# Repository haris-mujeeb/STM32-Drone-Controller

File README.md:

# 🚁 STM32 Drone Controller 🚀

A compact and robust drone flight controller designed with STM32 microcontroller and KiCad. This project focuses on providing a reliable hardware platform for custom drone builds and research.

## ✨ Features

*   **STM32 Microcontroller**: High-performance processing for flight control algorithms.
*   **BMI088 IMU**: Integrated 6-axis Inertial Measurement Unit for precise attitude estimation.
*   **KiCad Design**: Open-source hardware design files for easy modification and manufacturing.

## 🛠️ Technologies Used

*   **KiCad**: PCB design and schematic capture.
*   **STM32**: Embedded system development.
*   **BMI088**: Sensor integration.

## 📸 Visuals

## 📍Pinout

## 📄Schematic

## 📂 Project Structure

The repository contains all necessary KiCad project files, component libraries, and documentation.

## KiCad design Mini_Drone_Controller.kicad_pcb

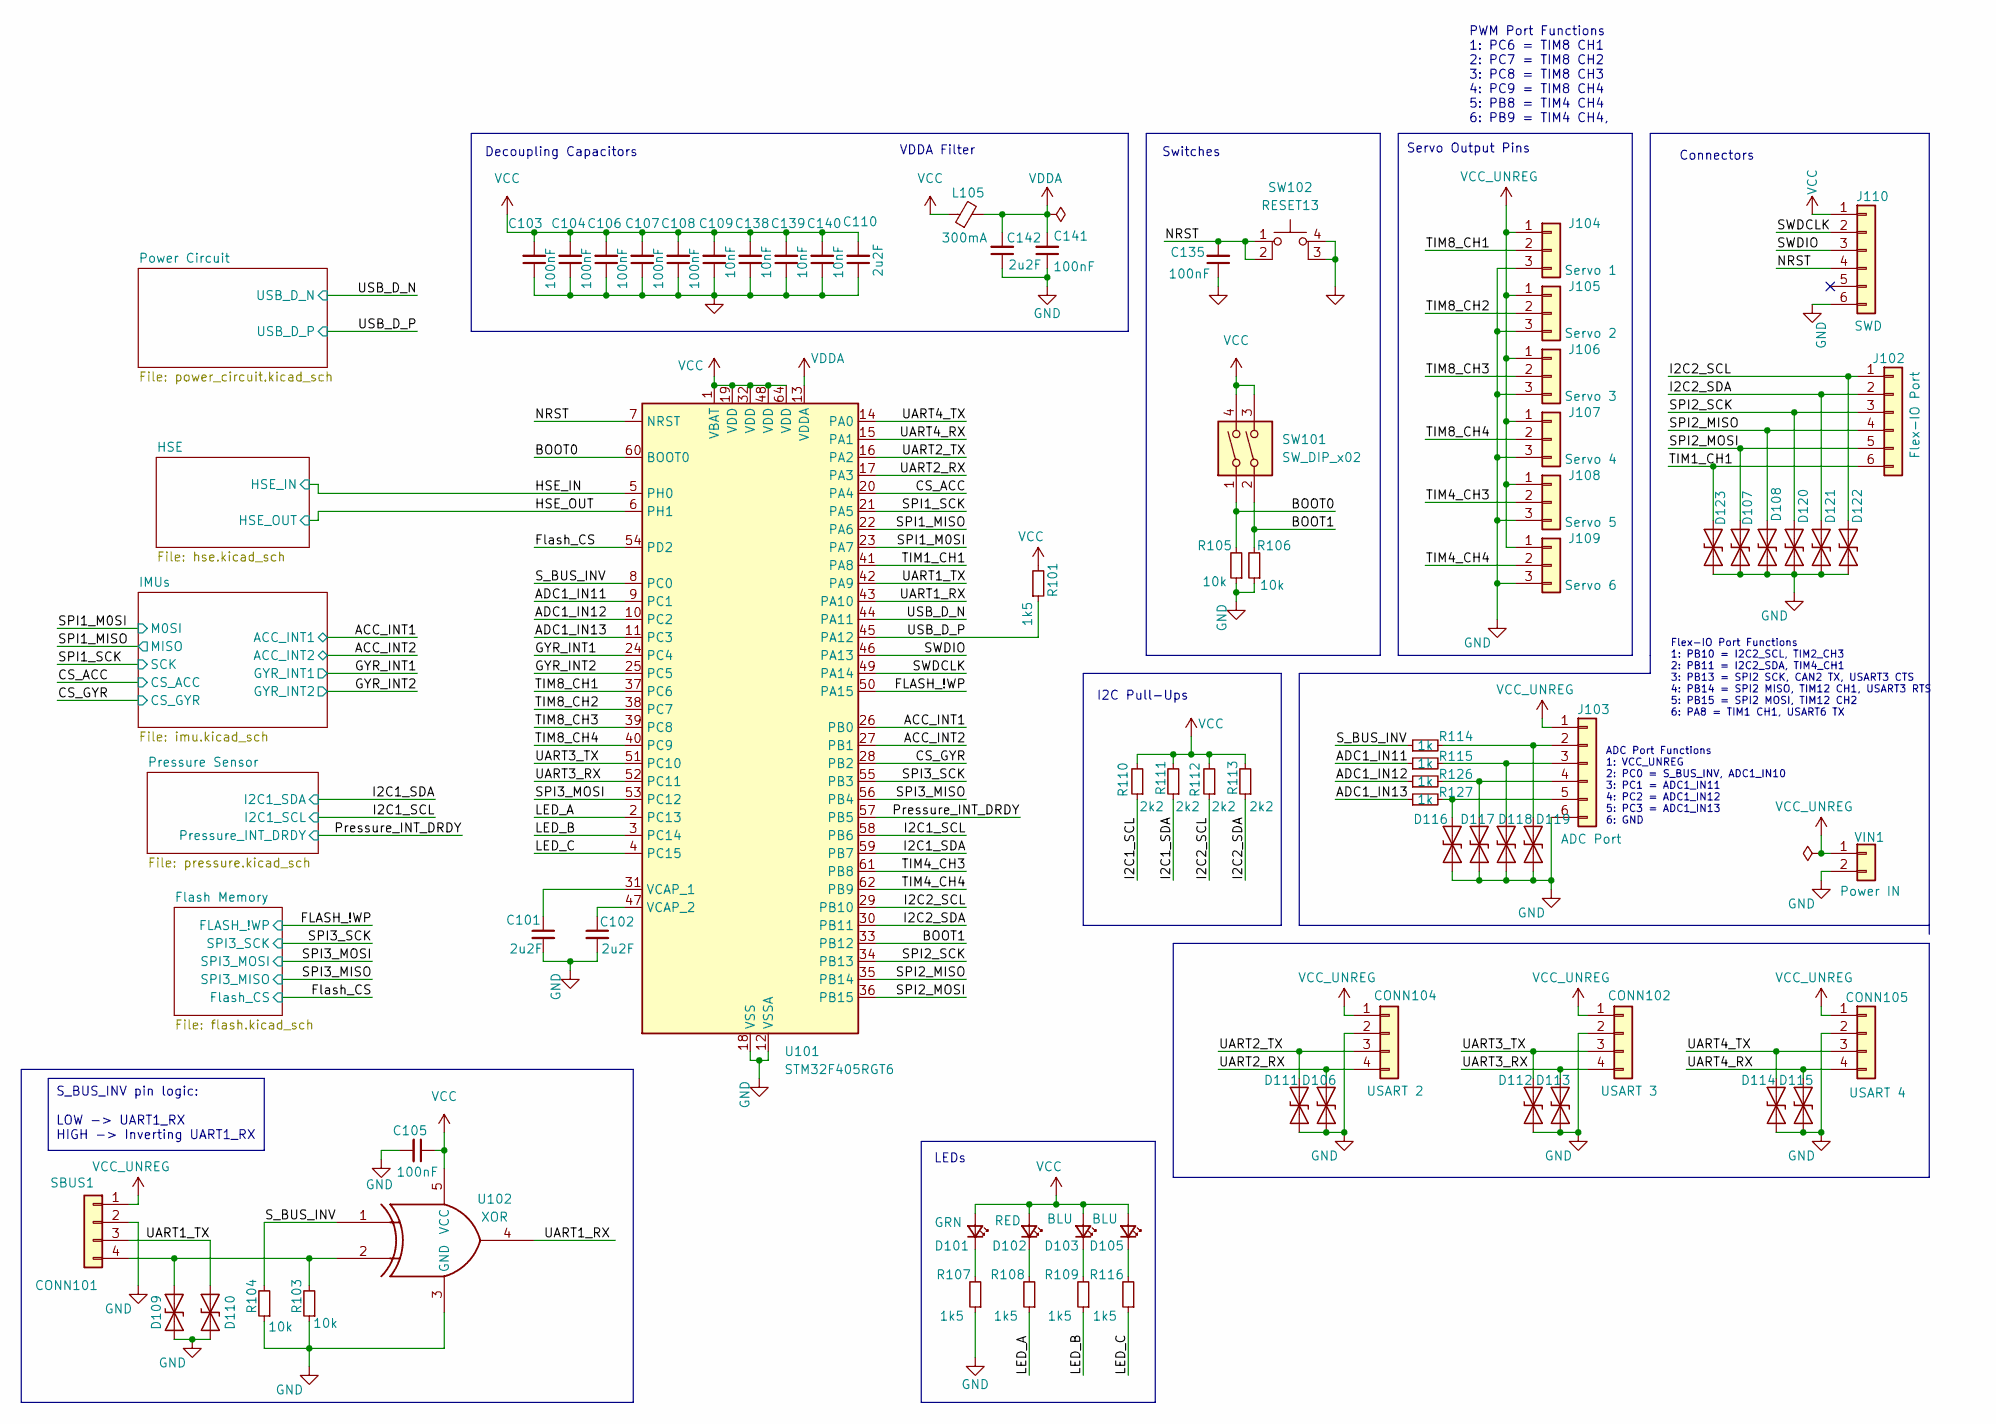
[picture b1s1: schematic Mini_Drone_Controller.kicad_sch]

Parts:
C101, C102, C110, C142: 2u2F; C_0402_1005Metric; Mfr. # CL05A225MQ5NSNC
C103, C104, C105, C106, C107, C108, C135, C141: 100nF; C_0402_1005Metric; Mfr. # CL05B104KO5NNNC
C109, C138, C139, C140: 10nF; C_0402_1005Metric; Mfr. # CL05B103KB5NNNC
CONN101: SBUS1; PinHeader_1x04_P2.54mm_Vertical; Mfr. # HB-PH3-25414PB2GOP
CONN102: USART 3; PinHeader_1x04_P2.54mm_Vertical; Mfr. # HB-PH3-25414PB2GOP
CONN104: USART 2; PinHeader_1x04_P2.54mm_Vertical; Mfr. # HB-PH3-25414PB2GOP
CONN105: USART 4; PinHeader_1x04_P2.54mm_Vertical; Mfr. # HB-PH3-25414PB2GOP
D101: GRN; LED_0603_1608Metric; Mfr. # PSC-1608U52GC-G4
D102: RED; LED_0603_1608Metric; Mfr. # XL-1608SURC-06
D103, D105: BLU; LED_0603_1608Metric; Mfr. # XL-1608UBC-04
D106, D107, D108, D109, D110, D111, D112, D113, D114, D115, D116, D117, D118, D119, D120, D121, D122, D123: ESD9B3.3ST5G; D_SOD-923; Mfr. # ESD9B3.3ST5G
J102: Flex-IO Port; PinHeader_1x06_P2.54mm_Vertical; Mfr. # PZ254V-11-06P
J103: ADC Port; PinHeader_1x06_P2.54mm_Vertical; Mfr. # PZ254V-11-06P
J104: Servo 1; PinHeader_1x03_P2.54mm_Vertical; Mfr. # 2.54-1*3P
J105: Servo 2; PinHeader_1x03_P2.54mm_Vertical; Mfr. # 2.54-1*3P
J106: Servo 3; PinHeader_1x03_P2.54mm_Vertical; Mfr. # 2.54-1*3P
J107: Servo 4; PinHeader_1x03_P2.54mm_Vertical; Mfr. # 2.54-1*3P
J108: Servo 5; PinHeader_1x03_P2.54mm_Vertical; Mfr. # 2.54-1*3P
J109: Servo 6; PinHeader_1x03_P2.54mm_Vertical; Mfr. # 2.54-1*3P
J110: SWD; PinHeader_1x06_P2.54mm_Vertical; Mfr. # PZ254V-11-06P
L105: 300mA; R_0402_1005Metric; Mfr. # BLM15AG102SN1D
R101, R107, R108, R109, R116: 1k5; R_0402_1005Metric; Mfr. # RC0402FR-071K5L
R103, R104, R105, R106: 10k; R_0402_1005Metric; Mfr. # RC0402FR-0710KL
R110, R111, R112, R113: 2k2; R_0402_1005Metric; Mfr. # RC0402FR-072K2L
R114, R115, R126, R127: 1k; R_0402_1005Metric; Mfr. # RC0402FR-071KL
SW101: SW_DIP_x02; SW_DIP_SPSTx02_Slide_Copal_CHS-02B_W7.62mm_P1.27mm; Mfr. # DSHP02TSGET
SW102: RESET13; SW_DIP_SPSTx01_Slide_Copal_CHS-01A_W5.08mm_P1.27mm_JPin; Mfr. # TS-1088-AR02016
U101: STM32F405RGT6; LQFP-64_10x10mm_P0.5mm; Mfr. # STM32F405RGT6
U102: XOR; SOT-353_SC-70-5; Mfr. # SN74LVC1G86DCKR
VIN1: Power IN; PinHeader_1x02_P2.54mm_Vertical; Mfr. # PZ254V-11-02P

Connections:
/ACC_INT1: U101.26 (PB0); also elsewhere on the board
/ACC_INT2: U101.27 (PB1); also elsewhere on the board
/ADC1_IN11: R115.1, U101.9 (PC1)
/ADC1_IN12: R126.1, U101.10 (PC2)
/ADC1_IN13: R127.1, U101.11 (PC3)
/BOOT0: R105.2, SW101.1, U101.60 (BOOT0)
/BOOT1: R106.2, SW101.2, U101.33 (PB12)
/CS_ACC: U101.20 (PA4); also elsewhere on the board
/CS_GYR: U101.28 (PB2); also elsewhere on the board
/FLASH_!WP: U101.50 (PA15); also elsewhere on the board
/Flash_CS: U101.54 (PD2); also elsewhere on the board
/GYR_INT1: U101.24 (PC4); also elsewhere on the board
/GYR_INT2: U101.25 (PC5); also elsewhere on the board
/HSE_IN: U101.5 (PH0); also elsewhere on the board
/HSE_OUT: U101.6 (PH1); also elsewhere on the board
/I2C1_SCL: R110.1, U101.58 (PB6); also elsewhere on the board
/I2C1_SDA: R111.1, U101.59 (PB7); also elsewhere on the board
/I2C2_SCL: D122.2 (A2), J102.1, R112.1, U101.29 (PB10)
/I2C2_SDA: D121.2 (A2), J102.2, R113.1, U101.30 (PB11)
/LED_A: R108.1, U101.2 (PC13)
/LED_B: R109.1, U101.3 (PC14)
/LED_C: R116.1, U101.4 (PC15)
/NRST: C135.2, J110.4, SW102.1, SW102.2, U101.7 (NRST)
/Pressure_INT_DRDY: U101.57 (PB5); also elsewhere on the board
/SPI1_M0SI: U101.23 (PA7); also elsewhere on the board
/SPI1_MISO: U101.22 (PA6); also elsewhere on the board
/SPI1_SCK: U101.21 (PA5); also elsewhere on the board
/SPI2_MISO: D108.2 (A2), J102.4, U101.35 (PB14)
/SPI2_MOSI: D107.2 (A2), J102.5, U101.36 (PB15)
/SPI2_SCK: D120.2 (A2), J102.3, U101.34 (PB13)
/SPI3_MISO: U101.56 (PB4); also elsewhere on the board
/SPI3_MOSI: U101.53 (PC12); also elsewhere on the board
/SPI3_SCK: U101.55 (PB3); also elsewhere on the board
/SWDCLK: J110.2, U101.49 (PA14)
/SWDIO: J110.3, U101.46 (PA13)
/S_BUS_INV: R104.2, R114.1, U101.8 (PC0), U102.1
/TIM1_CH1: D123.2 (A2), J102.6, U101.41 (PA8)
/TIM4_CH3: J108.2, U101.61 (PB8)
/TIM4_CH4: J109.2, U101.62 (PB9)
/TIM8_CH1: J104.2, U101.37 (PC6)
/TIM8_CH2: J105.2, U101.38 (PC7)
/TIM8_CH3: J106.2, U101.39 (PC8)
/TIM8_CH4: J107.2, U101.40 (PC9)
/UART1_RX: U101.43 (PA10), U102.4
/UART1_TX: CONN101.3, D110.2 (A2), U101.42 (PA9)
/UART2_RX: CONN104.4, D106.2 (A2), U101.17 (PA3)
/UART2_TX: CONN104.3, D111.2 (A2), U101.16 (PA2)
/UART3_RX: CONN102.4, D113.2 (A2), U101.52 (PC11)
/UART3_TX: CONN102.3, D112.2 (A2), U101.51 (PC10)
/UART4_RX: CONN105.4, D115.2 (A2), U101.15 (PA1)
/UART4_TX: CONN105.3, D114.2 (A2), U101.14 (PA0)
/USB_D_N: U101.44 (PA11); also elsewhere on the board
/USB_D_P: R101.1, U101.45 (PA12); also elsewhere on the board
GND: C101.2, C102.2, C103.1, C104.1, C105.2, C106.1, C107.1, C108.1, C109.1, C110.1, C135.1, C138.1, C139.1, C140.1, C141.1, C142.1, CONN101.2, CONN102.2, CONN104.2, CONN105.2, D106.1 (A1), D107.1 (A1), D108.1 (A1), D109.1 (A1), D110.1 (A1), D111.1 (A1), D112.1 (A1), D113.1 (A1), D114.1 (A1), D115.1 (A1), D116.1 (A1), D117.1 (A1), D118.1 (A1), D119.1 (A1), D120.1 (A1), D121.1 (A1), D122.1 (A1), D123.1 (A1), J103.6, J104.3, J105.3, J106.3, J107.3, J108.3, J109.3, J110.6, R103.1, R104.1, R105.1, R106.1, R107.1, SW102.3 (K), SW102.4 (A), U101.12 (VSSA), U101.18 (VSS), U101.63 (VSS), U102.3 (GND), VIN1.2; also elsewhere on the board
unnamed: CONN101.4, D109.2 (A2), R103.2, U102.2
unnamed: D101.1 (K), R107.2
unnamed: D102.1 (K), R108.2
unnamed: D103.1 (K), R109.2
unnamed: D105.1 (K), R116.2
unnamed: D116.2 (A2), J103.5, R127.2
unnamed: D117.2 (A2), J103.4, R126.2
unnamed: D118.2 (A2), J103.3, R115.2
unnamed: D119.2 (A2), J103.2, R114.2
unnamed: C101.1, U101.31 (VCAP_1)
unnamed: C102.1, U101.47 (VCAP_2)
VCC: C103.2, C104.2, C105.1, C106.2, C107.2, C108.2, C109.2, C110.2, C138.2, C139.2, C140.2, D101.2 (A), D102.2 (A), D103.2 (A), D105.2 (A), J110.1, L105.1, R101.2, R110.2, R111.2, R112.2, R113.2, SW101.3, SW101.4, U101.1 (VBAT), U101.19 (VDD), U101.32 (VDD), U101.48 (VDD), U101.64 (VDD), U102.5 (VCC); also elsewhere on the board
VCC_UNREG: CONN101.1, CONN102.1, CONN104.1, CONN105.1, J103.1, J104.1, J105.1, J106.1, J107.1, J108.1, J109.1, VIN1.1; also elsewhere on the board
VDDA: C141.2, C142.2, L105.2, U101.13 (VDDA)

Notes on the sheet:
S_BUS_INV pin logic: LOW -> UART1_RX HIGH -> Inverting UART1_RX
LEDs
Switches
Connectors
Decoupling Capacitors
VDDA Filter
Flex-IO Port Functions 1: PB10 = I2C2_SCL, TIM2_CH3 2: PB11 = I2C2_SDA, TIM4_CH1 3: PB13 = SPI2 SCK, CAN2 TX, USART3 CTS 4: PB14 = SPI2 MISO, TIM12 CH1, USART3 RTS 5: PB15 = SPI2 MOSI, TIM12 CH2 6: PA8 = TIM1 CH1, USART6 TX
I2C Pull-Ups
PWM Port Functions 1: PC6 = TIM8 CH1 2: PC7 = TIM8 CH2 3: PC8 = TIM8 CH3 4: PC9 = TIM8 CH4 5: PB8 = TIM4 CH4 6: PB9 = TIM4 CH4,
ADC Port Functions 1: VCC_UNREG 2: PC0 = S_BUS_INV, ADC1_IN10 3: PC1 = ADC1_IN11 4: PC2 = ADC1_IN12 5: PC3 = ADC1_IN13 6: GND
Servo Output Pins

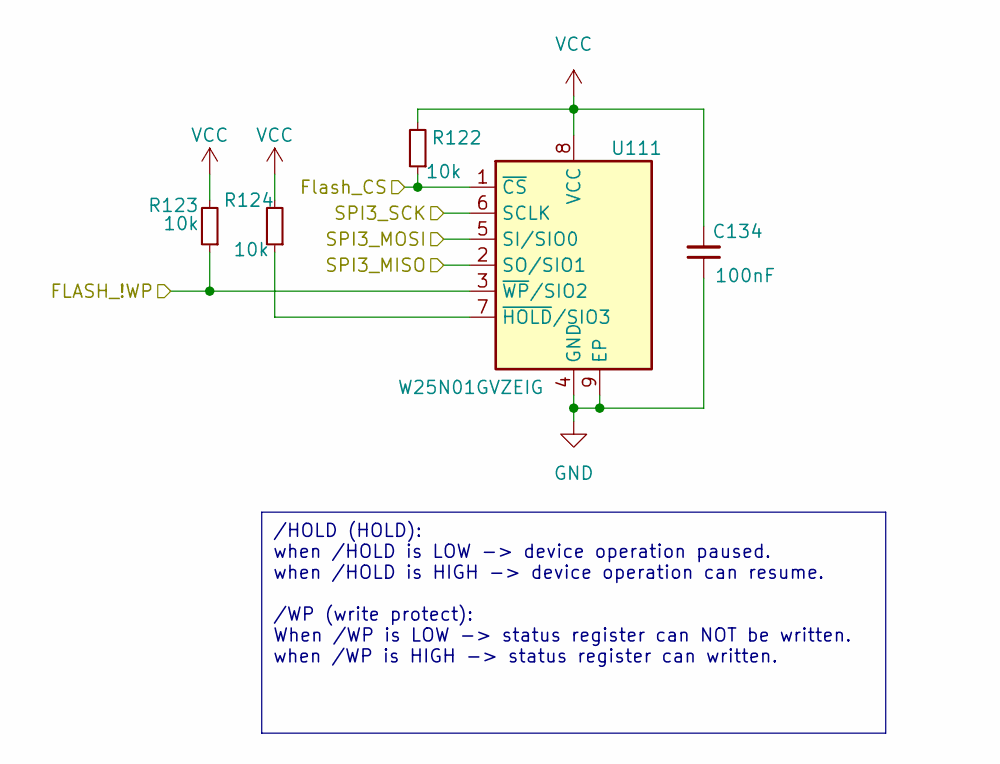
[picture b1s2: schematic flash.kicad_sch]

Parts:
C134: 100nF; C_0402_1005Metric; Mfr. # CL05B104KO5NNNC
R122, R123, R124: 10k; R_0402_1005Metric; Mfr. # RC0402FR-0710KL
U111: W25N01GVZEIG; WSON-8-1EP_8x6mm_P1.27mm_EP3.4x4.3mm; Mfr. # W25N01GVZEIG

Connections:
/FLASH_!WP: R123.1, U111.3 (~WP/SIO2); also elsewhere on the board
/Flash_CS: R122.1, U111.1 (~CS); also elsewhere on the board
/SPI3_MISO: U111.2 (SO/SIO1); also elsewhere on the board
/SPI3_MOSI: U111.5 (SI/SIO0); also elsewhere on the board
/SPI3_SCK: U111.6 (SCLK); also elsewhere on the board
GND: C134.1, U111.4 (GND), U111.9 (EP); also elsewhere on the board
unnamed: R124.1, U111.7 (~HOLD/SIO3)
VCC: C134.2, R122.2, R123.2, R124.2, U111.8 (VCC); also elsewhere on the board

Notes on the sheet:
/HOLD (HOLD): when /HOLD is LOW -> device operation paused. when /HOLD is HIGH -> device operation can resume. /WP (write protect): When /WP is LOW -> status register can NOT be written. when /WP is HIGH -> status register can written.

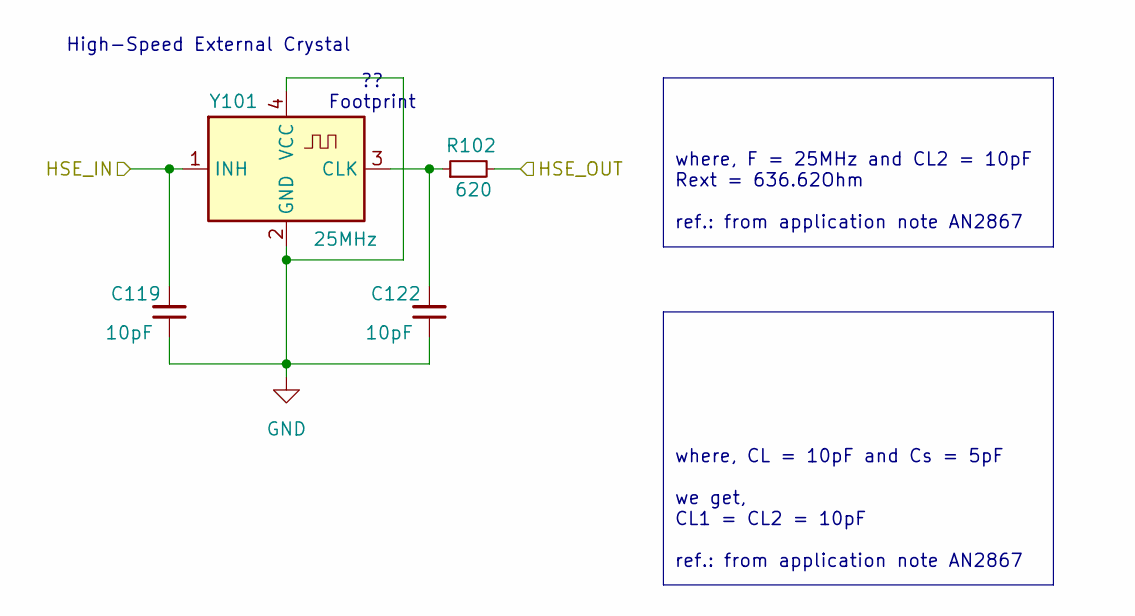
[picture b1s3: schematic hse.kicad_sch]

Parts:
C119, C122: 10pF; C_0402_1005Metric; Mfr. # CL05C100JB5NNNC
R102: 620; R_0402_1005Metric; Mfr. # RC0402FR-07620RL
Y101: 25MHz; Oscillator_SMD_Kyocera_KC2520Z-4Pin_2.5x2.0mm; Mfr. # X322525MSB4SI

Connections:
/HSE_IN: C119.2, Y101.1 (INH); also elsewhere on the board
/HSE_OUT: R102.2; also elsewhere on the board
GND: C119.1, C122.1, Y101.2 (GND), Y101.4 (VCC); also elsewhere on the board
unnamed: C122.2, R102.1, Y101.3 (CLK)

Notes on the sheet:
where, CL = 10pF and Cs = 5pF we get, CL1 = CL2 = 10pF ref.: from application note AN2867
where, F = 25MHz and CL2 = 10pF Rext = 636.62Ohm ref.: from application note AN2867
?? Footprint
High-Speed External Crystal

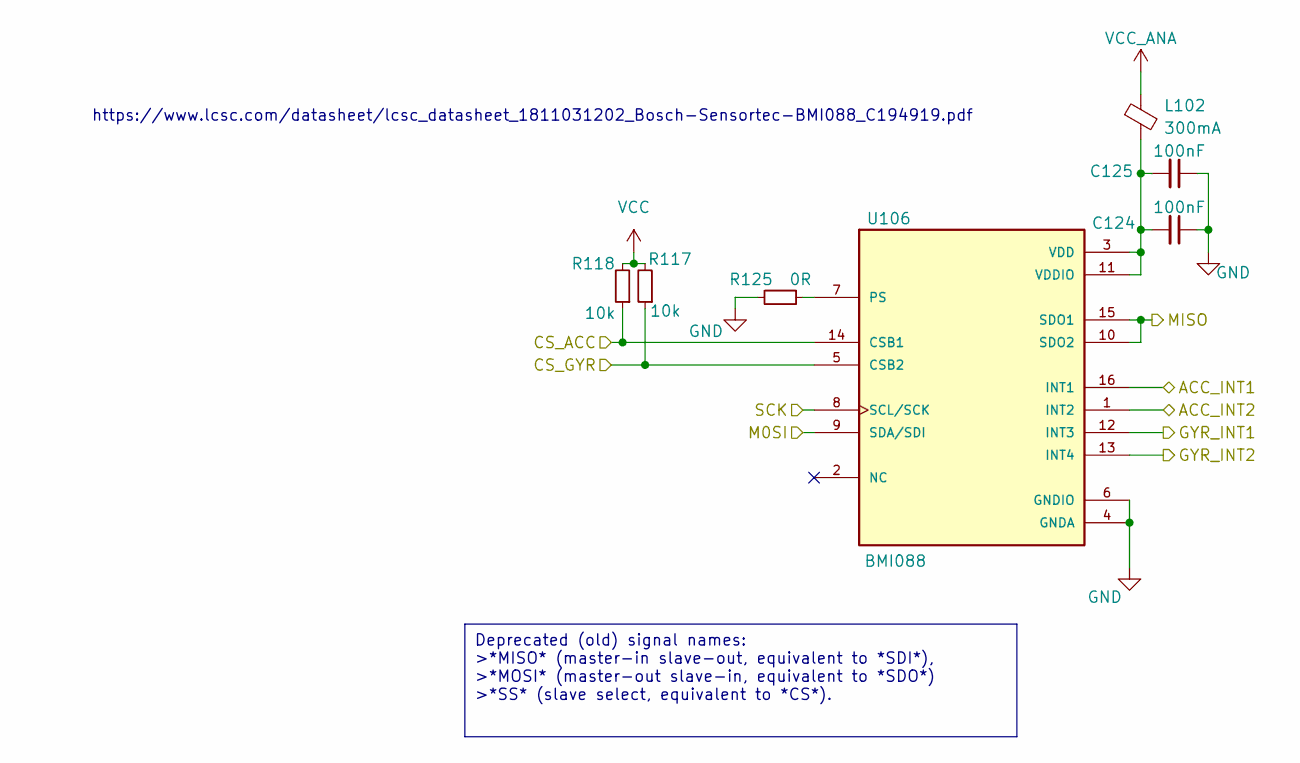
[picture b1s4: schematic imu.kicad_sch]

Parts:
C124, C125: 100nF; C_0402_1005Metric; Mfr. # CL05B104KO5NNNC
L102: 300mA; R_0402_1005Metric; Mfr. # BLM15AG102SN1D
R117, R118: 10k; R_0402_1005Metric; Mfr. # RC0402FR-0710KL
R125: 0R; R_0402_1005Metric; Mfr. # RC0402JR-070RL
U106: BMI088; PQFN50P450X300X100-16N; Mfr. # BMI088

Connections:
/ACC_INT1: U106.16 (INT1); also elsewhere on the board
/ACC_INT2: U106.1 (INT2); also elsewhere on the board
/CS_ACC: R118.1, U106.14 (CSB1); also elsewhere on the board
/CS_GYR: R117.1, U106.5 (CSB2); also elsewhere on the board
/GYR_INT1: U106.12 (INT3); also elsewhere on the board
/GYR_INT2: U106.13 (INT4); also elsewhere on the board
/SPI1_M0SI: U106.9 (SDA/SDI); also elsewhere on the board
/SPI1_MISO: U106.10 (SDO2), U106.15 (SDO1); also elsewhere on the board
/SPI1_SCK: U106.8 (SCL/SCK); also elsewhere on the board
GND: C124.1, C125.1, R125.2, U106.4 (GNDA), U106.6 (GNDIO); also elsewhere on the board
unnamed: R125.1, U106.7 (PS)
unnamed: C124.2, C125.2, L102.2, U106.3 (VDD), U106.11 (VDDIO)
VCC: R117.2, R118.2; also elsewhere on the board
VCC_ANA: L102.1; also elsewhere on the board

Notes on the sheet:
Deprecated (old) signal names: >*MISO* (master-in slave-out, equivalent to *SDI*), >*MOSI* (master-out slave-in, equivalent to *SDO*) >*SS* (slave select, equivalent to *CS*).
https://www.lcsc.com/datasheet/lcsc_datasheet_1811031202_Bosch-Sensortec-BMI088_C194919.pdf

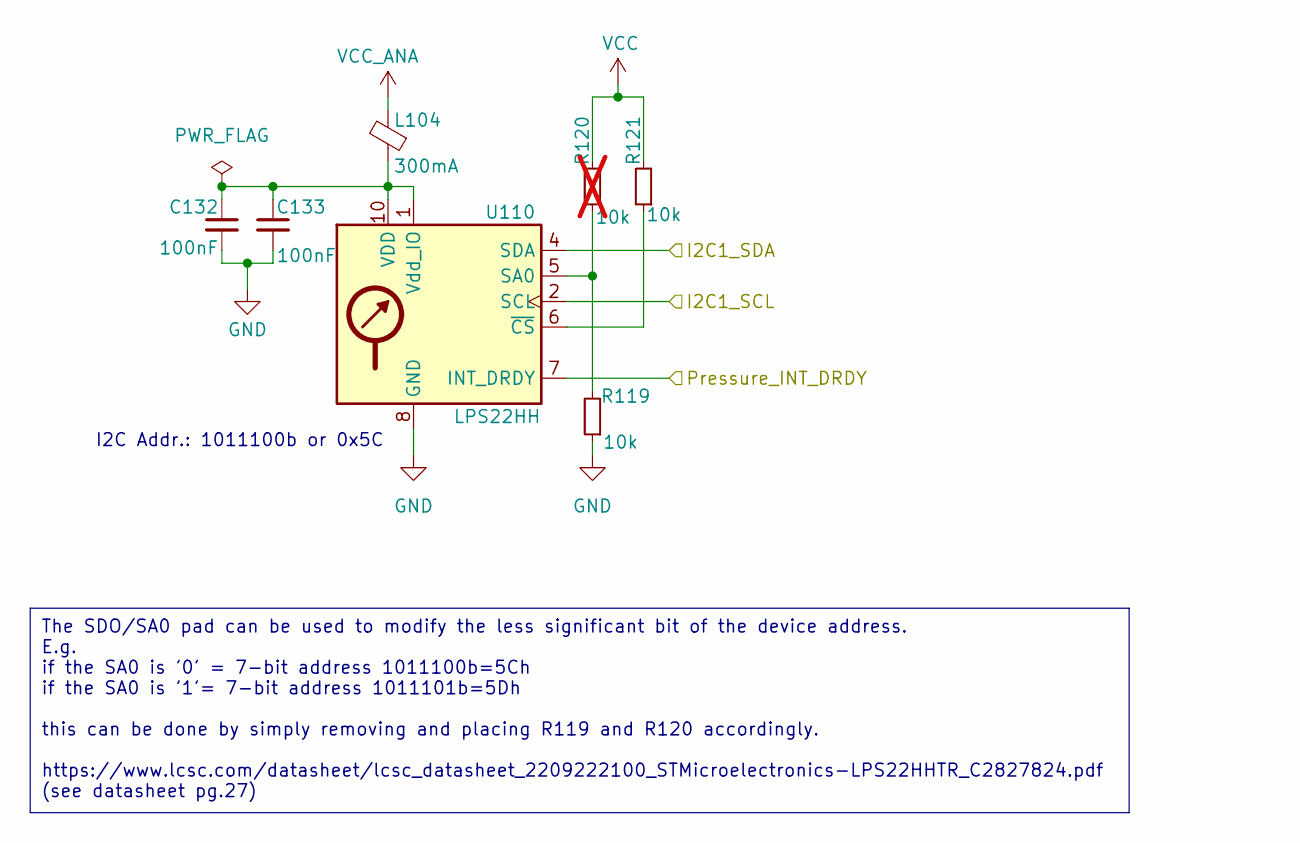
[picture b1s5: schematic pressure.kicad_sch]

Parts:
C132, C133: 100nF; C_0402_1005Metric; Mfr. # CL05B104KO5NNNC
L104: 300mA; R_0402_1005Metric; Mfr. # BLM15AG102SN1D
R119, R121: 10k; R_0402_1005Metric; Mfr. # RC0402FR-0710KL
R120: 10k; R_0402_1005Metric; Mfr. # RC0402FR-0710KL; not fitted
U110: LPS22HH; ST_HLGA-10_2x2mm_P0.5mm_LayoutBorder3x2y; Mfr. # LPS22HHTR

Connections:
/I2C1_SCL: U110.2 (SCL); also elsewhere on the board
/I2C1_SDA: U110.4 (SDA); also elsewhere on the board
/Pressure_INT_DRDY: U110.7 (INT_DRDY); also elsewhere on the board
GND: C132.2, C133.2, R119.1, U110.3 (GND), U110.8 (GND), U110.9 (GND); also elsewhere on the board
unnamed: R119.2, R120.1, U110.5 (SA0)
unnamed: C132.1, C133.1, L104.1, U110.1 (Vdd_IO), U110.10 (VDD)
unnamed: R121.1, U110.6 (~CS)
VCC: R120.2, R121.2; also elsewhere on the board
VCC_ANA: L104.2; also elsewhere on the board

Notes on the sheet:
The SDO/SA0 pad can be used to modify the less significant bit of the device address. E.g. if the SA0 is '0' = 7-bit address 1011100b=5Ch if the SA0 is '1'= 7-bit address 1011101b=5Dh this can be done by simply removing and placing R119 and R120 accordingly. https://www.lcsc.com/datasheet/lcsc_data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
I2C Addr.: 1011100b or 0x5C

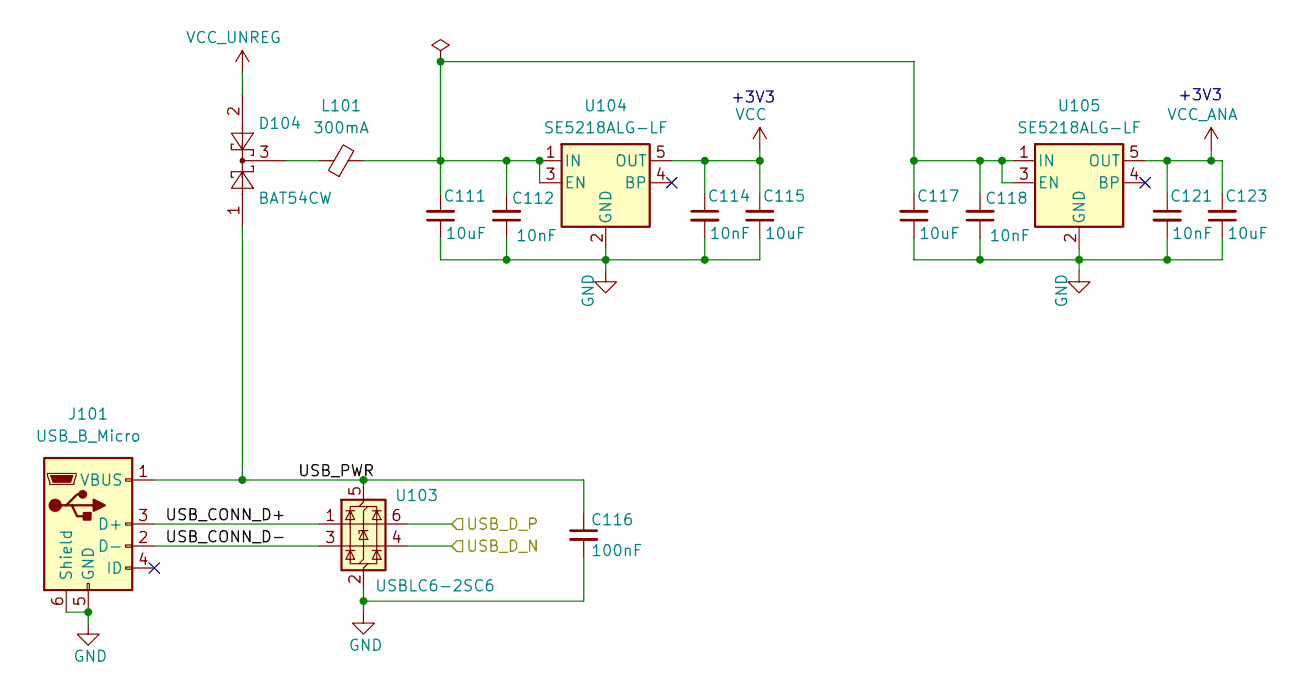
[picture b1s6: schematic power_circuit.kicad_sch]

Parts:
C111, C115, C117, C123: 10uF; C_0402_1005Metric; Mfr. # CL05A106MQ5NUNC
C112, C114, C118, C121: 10nF; C_0402_1005Metric; Mfr. # CL05B103KB5NNNC
C116: 100nF; C_0402_1005Metric; Mfr. # CL05B104KO5NNNC
D104: BAT54CW; SOT-323_SC-70
J101: USB_B_Micro; USB_Micro-AB_Molex_47590-0001; Mfr. # 475900001
L101: 300mA; R_0402_1005Metric; Mfr. # BLM15AG102SN1D
U103: USBLC6-2SC6; SOT-23-6; Mfr. # USBLC6-2SC6
U104, U105: SE5218ALG-LF; SOT-23-5; Mfr. # SE5218ALG-LF

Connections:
/Power Circuit/USB_CONN_D+: J101.3 (D+), U103.1 (I/O1)
/Power Circuit/USB_CONN_D-: J101.2 (D-), U103.3 (I/O2)
/Power Circuit/USB_PWR: C116.1, D104.1, J101.1 (VBUS), U103.5 (VBUS)
/USB_D_N: U103.4 (I/O2); also elsewhere on the board
/USB_D_P: U103.6 (I/O1); also elsewhere on the board
GND: C111.1, C112.1, C114.2, C115.1, C116.2, C117.1, C118.1, C121.2, C123.1, J101.5 (GND), J101.6 (Shield), U103.2 (GND), U104.2 (GND), U105.2 (GND); also elsewhere on the board
unnamed: D104.3, L101.1
unnamed: C111.2, C112.2, C117.2, C118.2, L101.2, U104.1 (IN), U104.3 (EN), U105.1 (IN), U105.3 (EN)
VCC: C114.1, C115.2, U104.5 (OUT); also elsewhere on the board
VCC_ANA: C121.1, C123.2, U105.5 (OUT); also elsewhere on the board
VCC_UNREG: D104.2; also elsewhere on the board

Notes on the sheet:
+3V3

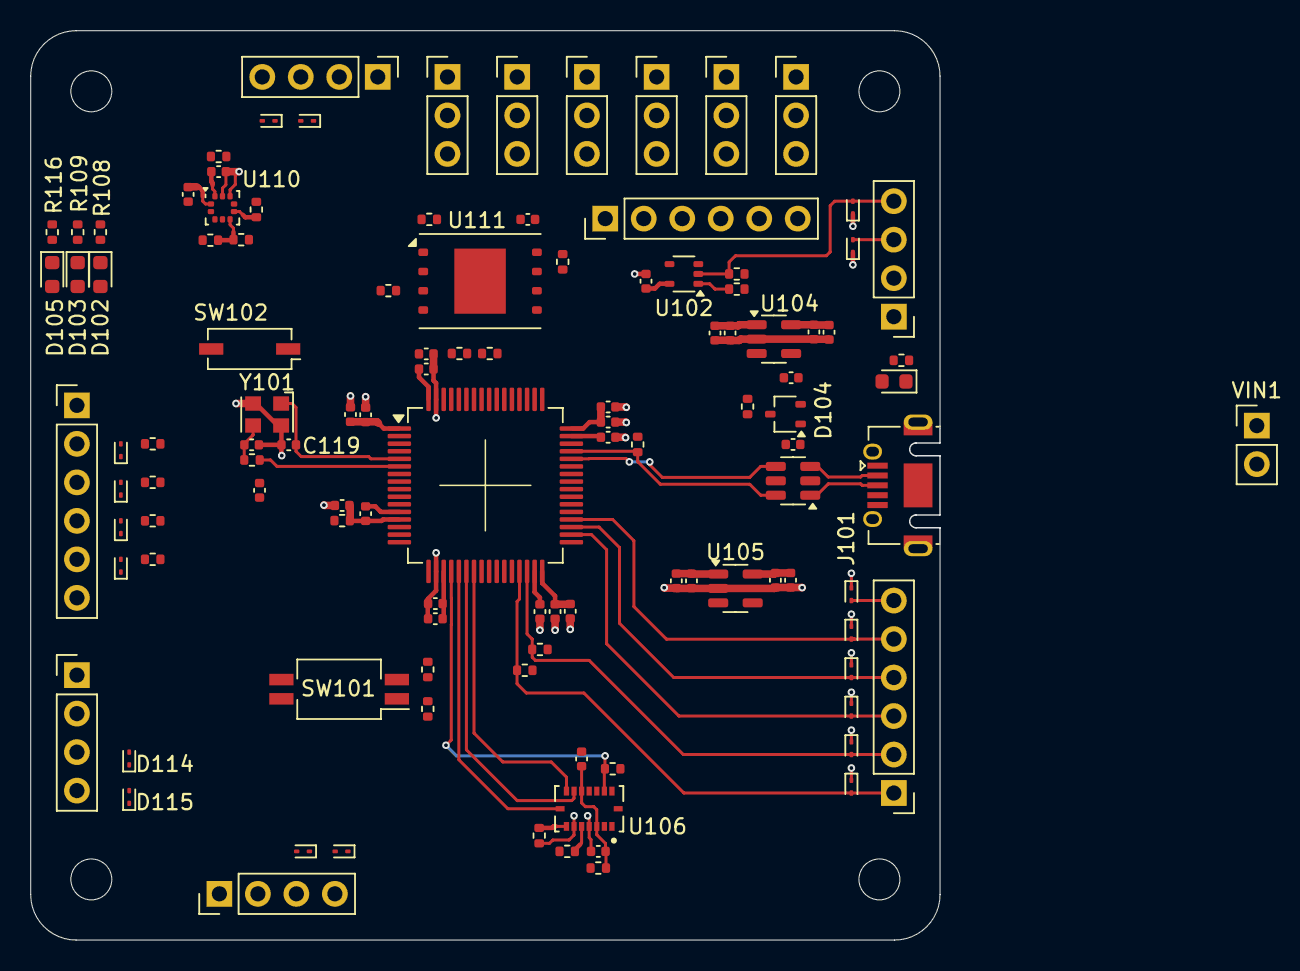
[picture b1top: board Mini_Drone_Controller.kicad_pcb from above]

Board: 4 copper layers, 60.0 x 60.0 mm, 113 parts (0 on the bottom side), 81 nets.

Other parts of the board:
C113: 10nF; C_0402_1005Metric

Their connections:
GND: C113.1; also elsewhere on the board

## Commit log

2025-10-25 v1.0
2025-10-25 Update README with pinout and schematic visuals
    Added pinout and schematic sections with images.
